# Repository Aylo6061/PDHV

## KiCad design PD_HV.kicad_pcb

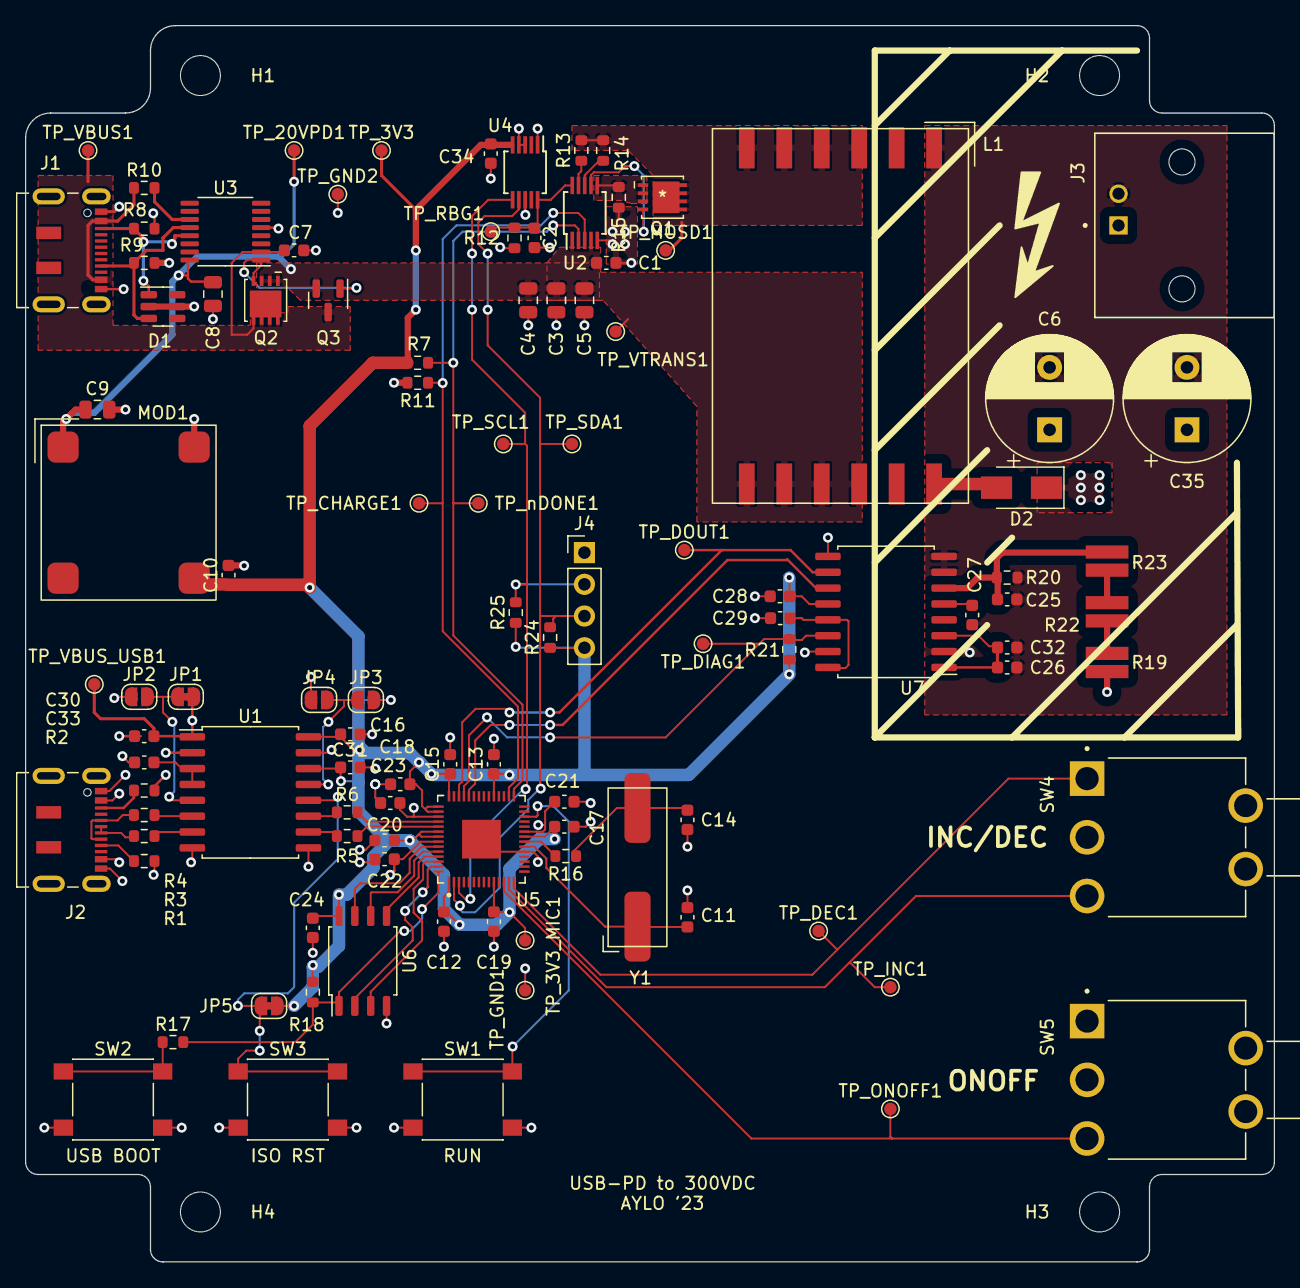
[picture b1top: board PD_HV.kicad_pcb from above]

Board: 4 copper layers, 100.0 x 99.0 mm, 112 parts (0 on the bottom side), 61 nets.

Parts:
C1: 10u; C_0603_1608Metric
C2: 100pF; C_0603_1608Metric
C3, C4, C5: 22uF; C_0805_2012Metric
C6, C35: 3.3u; CP_Radial_D10.0mm_P5.00mm
C7, C12, C21, C26, C28: 1uF; C_0603_1608Metric
C8, C9: 10uF; C_0805_2012Metric
C10: 22uF; C_0603_1608Metric
C11, C14: 27p; C_0603_1608Metric
C13, C15, C16, C17, C18, C19, C20, C22, C23, C24, C27, C29, C30, C31, C32, C33, C34: 100nF; C_0603_1608Metric
C25: 1nF; C_0603_1608Metric
D1: ESDA6V1BC6; SOT-23-6
D2: 600V; D_SMA
H1, H2, H3, H4: MountingHole; MountingHole_3.2mm_M3
J1, J2: USB_C_Receptacle; USB_C_Receptacle_JAE_DX07S016JA1R1500
J3: Conn_Coaxial; TE_5227161-2
J4: Conn_01x04_Male; PinHeader_1x04_P2.54mm_Vertical
JP1, JP5: SolderJumper-2_P1.3mm_Bridged_RoundedPad1.0x1.5mm
JP2, JP3, JP4: SolderJumper-2_P1.3mm_Open_RoundedPad1.0x1.5mm
L1: DA2034-AL
MOD1: K7803JT-500R3-LB; MORNSUN_K7803JT-500R3-LB
Q1: AON7296; DFN3X3A_8L_EPA1_P_AOS
Q2: AON7410; DFN3X3A_8L_EPA1_P_AOS
Q3: AO3400A; SOT-23
R1, R2, R8, R9: 5.1k; R_0603_1608Metric
R3, R4, R5, R6: 24; R_0603_1608Metric
R7, R11, R18: 10k; R_0603_1608Metric
R10: 100k; R_0603_1608Metric
R12: R; R_0603_1608Metric
R13: 12k 1%; R_0603_1608Metric
R14: 43k 1%; R_0603_1608Metric
R15: .024 Ohm 1% 1/3W; R_0603_1608Metric
R16, R17, R20: 1k; R_0603_1608Metric
R19, R22, R23: 100k; RESC1632X60N
R21, R24, R25: 4k7; R_0603_1608Metric
SW1, SW2, SW3: SW_SPST; SW_SPST_PTS645
SW4: MOM-OFF-MOM; SW_100SP1T2B4M6QE
SW5: SW_SPDT; SW_100SP1T2B4M6QE
TP_3V3, TP_3V3_MIC1, TP_20VPD1: TestPoint; TestPoint_Pad_D1.0mm
TP_CHARGE1: TestPoint; TestPoint_Pad_D1.0mm
TP_DEC1: TestPoint; TestPoint_Pad_D1.0mm
TP_DIAG1: TestPoint; TestPoint_Pad_D1.0mm
TP_DOUT1: TestPoint; TestPoint_Pad_D1.0mm
TP_GND1, TP_GND2: TestPoint; TestPoint_Pad_D1.0mm
TP_INC1: TestPoint; TestPoint_Pad_D1.0mm
TP_MOSD1: TestPoint; TestPoint_Pad_D1.0mm
TP_ONOFF1: TestPoint; TestPoint_Pad_D1.0mm
TP_RBG1: TestPoint; TestPoint_Pad_D1.0mm
TP_SCL1: TestPoint; TestPoint_Pad_D1.0mm
TP_SDA1: TestPoint; TestPoint_Pad_D1.0mm
TP_VBUS1: TestPoint; TestPoint_Pad_D1.0mm
TP_VBUS_USB1: TestPoint; TestPoint_Pad_D1.0mm
TP_VTRANS1: TestPoint; TestPoint_Pad_D1.0mm
TP_nDONE1: TestPoint; TestPoint_Pad_D1.0mm
U1: SOIC-16W_7.5x10.3mm_P1.27mm
U2: LT3750A; MSOP-10_3x3mm_P0.5mm
U3: IP2721; TSSOP-16_4.4x5mm_P0.65mm
U4: AD5170BRMZ2.5; MSOP-10_3x3mm_P0.5mm
U5: RP2040; QFN40P700X700X90-57N
U6: W25Q128JVS; SOIC-8_5.23x5.23mm_P1.27mm
U7: AMC3336-Q1; SOIC-16W_7.5x10.3mm_P1.27mm
Y1: Crystal; ABLS-2SMD-XTAL

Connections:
+1V1: C21.1, C22.1, C23.1, U5.23 (DVDD), U5.45 (VREG_VOUT), U5.50 (DVDD)
+3.3V: C10.1, C12.1, C13.1, C15.1, C16.1, C17.1, C18.1, C19.1, C20.1, C24.1, C28.2, C31.1, C34.1, J4.4, JP3.2 (B), JP5.2 (B), MOD1.3 (+Vo_3V3), R7.1, R18.1, R21.1, R24.1, R25.1, TP_3V3.1, TP_3V3_MIC1.1, U1.14 (VDD2), U1.16 (VBUS2), U4.5 (VDD), U5.1 (IOVDD), U5.10 (IOVDD), U5.22 (IOVDD), U5.33 (IOVDD), U5.42 (IOVDD), U5.43 (ADC_AVDD), U5.44 (VREG_VIN), U5.48 (USB_VDD), U5.49 (IOVDD), U6.8 (VCC), U7.12 (VDD)
+20V_USBPD: C1.1, C3.1, C4.1, C5.1, C8.1, C9.1, L1.7, L1.8, L1.9, L1.10, MOD1.1 (+Vin), Q2.1 (S), Q2.2 (S), Q2.3 (S), Q3.2 (S), TP_20VPD1.1, TP_VTRANS1.1, U2.1 (VTRANS), U2.4 (Vcc), U3.16 (VBUS)
+HV: C6.1, C35.1, D2.1 (K), J3.1 (In), R19.1
+VBUS_USB: C30.1, J2.A4 (VBUS), J2.A9 (VBUS), J2.B4 (VBUS), J2.B9 (VBUS), JP1.2 (B), TP_VBUS_USB1.1, U1.1 (VBUS1)
/HVMeasurement/CLKIN: U5.38 (GPIO26/ADC0), U7.11 (CLKIN)
/HVMeasurement/DIAG: R21.2, TP_DIAG1.1, U5.39 (GPIO27/ADC1), U7.14 (DIAG)
/HVMeasurement/DOUT: TP_DOUT1.1, U5.40 (GPIO28/ADC2), U7.10 (DOUT)
/HV_Flyback/CHARGE: R11.1, TP_CHARGE1.1, U2.3 (CHARGE), U5.30 (GPIO19)
/HV_Flyback/RBG: C2.1, R12.1, TP_RBG1.1, U2.10 (RBG), U4.10 (W)
/HV_Flyback/nDone: R7.2, TP_nDONE1.1, U2.2 (nDONE), U5.29 (GPIO18)
/ISO_USB/HOST_DN: J2.A7 (D-), J2.B7 (D-), R4.1
/ISO_USB/HOST_DP: J2.A6 (D+), J2.B6 (D+), R3.1
/ISO_USB/ISO_DN: R6.2, U5.46 (USB_DM)
/ISO_USB/ISO_DP: R5.2, U5.47 (USB_DP)
/ISO_USB/PIN: JP5.1 (A), SW3.1 (A), U1.12 (PIN)
/ISO_USB/VDD1: C33.1, U1.3 (VDD1), U1.4 (PDEN)
/RP2040/DEC: SW4.1, TP_DEC1.1, U5.14 (GPIO11)
/RP2040/INC: SW4.3, TP_INC1.1, U5.13 (GPIO10)
/RP2040/ONOFF: SW5.3, TP_ONOFF1.1, U5.12 (GPIO9)
/RP2040/QSPI_SCLK: U5.52 (QSPI_SCLK), U6.6 (CLK)
/RP2040/QSPI_SD0: U5.53 (QSPI_SD0), U6.5 (DI(IO0))
/RP2040/QSPI_SD1: U5.55 (QSPI_SD1), U6.2 (DO(IO1))
/RP2040/QSPI_SD2: U5.54 (QSPI_SD2), U6.3 (IO2)
/RP2040/QSPI_SD3: U5.51 (QSPI_SD3), U6.7 (IO3)
/RP2040/QSPI_SS: R17.2, R18.2, U5.56 (QSPI_CSN), U6.1 (~CS)
/RP2040/RUN: SW1.1 (A), U5.26 (RUN)
/RP2040/SCL: J4.2, R25.2, TP_SCL1.1, U4.6 (SCL), U5.3 (GPIO1)
/RP2040/SDA: J4.3, R24.2, TP_SDA1.1, U4.7 (SDA), U5.2 (GPIO0)
/RP2040/nUSB_BOOT: R17.1, SW2.1 (A)
/USBPD_IN/CC1: D1.1 (TVS1), J1.A5 (CC1), R8.1, U3.13 (CC1)
/USBPD_IN/CC2: D1.3 (TVS2), J1.B5 (CC2), R9.1, U3.12 (CC2)
/USBPD_IN/VBUSG: Q2.4 (G), Q3.1 (G), U3.1 (VBUSG)
GND: C1.2, C2.2, C3.2, C4.2, C5.2, C7.2, C8.2, C9.2, C10.2, C11.2, C12.2, C13.2, C14.2, C15.2, C16.2, C17.2, C18.2, C19.2, C20.2, C21.2, C22.2, C23.2, C24.2, C28.1, C29.1, C31.2, C34.2, D1.2 (COM), D1.5 (COM), J1.A1 (GND), J1.A12 (GND), J1.B1 (GND), J1.B12 (GND), J4.1, JP4.1 (A), MOD1.4 (GND), R8.2, R9.2, R11.2, R12.2, R15.2, SW1.2 (B), SW2.2 (B), SW3.2 (B), SW4.2, SW5.2, TP_GND1.1, TP_GND2.1, U1.9 (GND2), U1.15 (GND2), U2.5 (GND), U3.5 (GND), U4.1 (B), U4.3 (AD0), U4.4 (GND), U4.8 (AD1), U5.19 (TESTEN), U5.57 (GND), U6.4 (GND), U7.9 (GND), U7.15 (DCDC_GND)
GND1: C30.2, C33.2, J2.A1 (GND), J2.A12 (GND), J2.B1 (GND), J2.B12 (GND), JP2.1 (A), R1.2, R2.2, U1.2 (GND1), U1.8 (GND1)
GND2: C6.2, C25.2, C26.1, C27.1, C32.2, C35.2, J3.2 (Ext), L1.1, R20.2, U7.2 (DCDC_HGND), U7.7 (INN), U7.8 (HGND)
unnamed: C11.1, U5.20 (XIN), Y1.1
unnamed: C14.1, R16.1, Y1.2
unnamed: C25.1, R20.1, R23.2, U7.6 (INP)
unnamed: C26.2, C32.1, U7.1 (DCDC_OUT), U7.3 (HLDO_IN)
unnamed: C27.2, U7.5 (HLDO_OUT)
unnamed: C29.2, U7.13 (LDO_OUT), U7.16 (DCDC_IN)
unnamed: D2.2 (A), L1.12
unnamed: J2.A5 (CC1), R2.1
unnamed: J2.B5 (CC2), R1.1
unnamed: JP1.1 (A), JP2.2 (B), U1.5 (SPU)
unnamed: JP3.1 (A), JP4.2 (B), U1.13 (SPD)
unnamed: L1.3, L1.4, L1.5, L1.6, Q1.5 (D), Q1.6 (D), Q1.7 (D), Q1.8 (D), R13.2, R14.2, TP_MOSD1.1
unnamed: Q1.1 (S), Q1.2 (S), Q1.3 (S), R15.1, U2.6 (SOURCE)
unnamed: Q1.4 (G), U2.7 (GATE)
unnamed: R3.2, U1.7 (UD+)
unnamed: R4.2, U1.6 (UD-)
unnamed: R5.1, U1.10 (DD+)
unnamed: R6.1, U1.11 (DD-)
unnamed: R10.2, U3.11 (SEL)
unnamed: R13.1, U2.9 (RVOUT)
unnamed: R14.1, U2.8 (RDCM)
unnamed: R16.2, U5.21 (XOUT)
unnamed: R19.2, R22.1
unnamed: R22.2, R23.1
VBUS: C7.1, J1.A4 (VBUS), J1.A9 (VBUS), J1.B4 (VBUS), J1.B9 (VBUS), Q2.5 (D), Q2.6 (D), Q2.7 (D), Q2.8 (D), Q3.3 (D), R10.1, TP_VBUS1.1, U3.2 (VIN)

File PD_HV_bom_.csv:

Component,Description,Part,References,Value,Footprint,Quantity Per PCB,Datasheet,MPN,Voltage,Digikey PN,Tol,MANUFACTURER,MAXIMUM_PACKAGE_HEIGHT,PARTREV,STANDARD
1,Unpolarized capacitor,C,C11 C14,27p,C_0603_1608Metric,2,~,CC0603JRNPO9BN270,,,,,,,
2,Unpolarized capacitor,C,C2,100pF,C_0603_1608Metric,1,~,CL10C101JB8NNNC,50V,,,,,,
3,Unpolarized capacitor,C,C25,1nF,,1,~,CL10B102KB8NNWC,,,,,,,
4,Unpolarized capacitor,C,C13 C15 C17 C18 C19 C20 C22 C23 C24 C34,100nF,C_0603_1608Metric,10,~,CC0603KRX7R6BB104,10V,,,,,,
5,Unpolarized capacitor,C,C16 C30 C31 C33,100nF,,4,~,CC0603KRX7R6BB104,10V,,,,,,
6,Unpolarized capacitor,C,C27 C29 C32,100nF,,3,~,CL10B104KB8NNWC,50V,,,,,,
7,Unpolarized capacitor,C,C12 C21,1uF,C_0603_1608Metric,2,~,CL10B105KP8NNNC,10V,,,,,,
8,Unpolarized capacitor,C,C26 C28,1uF,,2,~,CL10A105KB8NNNC,50V,,,,,,
9,Unpolarized capacitor,C,C7,1uF,C_0603_1608Metric,1,~,UMK107BJ105KA-T,25V,,,,,,
10,"Polarized capacitor, US symbol",C_Polarized_US,C6 C35,3.3u,CP_Radial_D10.0mm_P5.00mm,2,~,860021375011,400V,,,,,,
11,Unpolarized capacitor,C,C1,10u,C_0603_1608Metric,1,~,CL21A106KAYNNNG,25V,,,,,,
12,Unpolarized capacitor,C,C8 C9,10uF,C_0805_2012Metric,2,~,GRM21BR61H106KE43L,50V,,,,,,
13,Unpolarized capacitor,C,C10,22uF,C_0603_1608Metric,1,~,CL10A226MP8NUNE,10V,,,,,,
14,Unpolarized capacitor,C,C3 C4 C5,22uF,C_0805_2012Metric,3,~,CL21A226MAYNNNE,25V,,,,,,
15,Diode,D,D2,600V,D_SMA,1,~,ES1J,600V,1655-ES1JCT-ND,,,,,
16,"Quad bidirectional transil, Suppressor for ESD protection, 5V Standoff, 4 Channels, SOT-23-6",ESDA6V1BC6,D1,ESDA6V1BC6,SOT-23-6,1,http://www.st.com/content/ccc/resource/technical/document/da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,ESDA6V1BC6,,,,,,,
17,"Generic connector, single row, 01x04, script generated (kicad-library-utils/schlib/autogen/connector/)",Conn_01x04_Male,J4,Conn_01x04_Male,PinHeader_1x04_P2.54mm_Vertical,1,~,,,,,,,,
18,"coaxial connector (BNC, SMA, SMB, SMC, Cinch/RCA, LEMO, ...)",Conn_Coaxial,J3,Conn_Coaxial,TE_5227161-2,1, ~,5227161-2,,,,,,,
19,USB Full-Featured Type-C Receptacle connector,USB_C_Receptacle,J1,USB_C_Receptacle,USB_C_Receptacle_JAE_DX07S016JA1R1500,1,https://www.usb.org/sites/default/files/documents/usb_type-c.zip,DX07S016JA1R1500,,,,,,,
20,USB Full-Featured Type-C Receptacle connector,USB_C_Receptacle,J2,USB_C_Receptacle,,1,https://www.usb.org/sites/default/files/documents/usb_type-c.zip,DX07S016JA1R1500,,,,,,,
21,"Solder Jumper, 2-pole, open",SolderJumper_2_Open,JP2 JP4,~,,2,~,DNP,,,,,,,
22,Flyback transformer 10:1 5A max,DA2034-AL,L1,DA2034-AL,DA2034-AL,1,,DA2034-AL,,,,,,,
23,,K7803JT-500R3-LB,MOD1,K7803JT-500R3-LB,MORNSUN_K7803JT-500R3-LB,1,,K7803JT-500R3-LB,,,,,,,
24,"30V Vds, 5.7A Id, N-Channel MOSFET, SOT-23",AO3400A,Q3,AO3400A,SOT-23,1,http://www.aosmd.com/pdfs/datasheet/AO3400A.pdf,AO3400A,,,,,,,
25,,AON7296,Q1,AON7296,DFN3X3A_8L_EPA1_P_AOS,1,,AON7296,,,,,,,
26,,AON7410,Q2,AON7410,DFN3X3A_8L_EPA1_P_AOS,1,,AON7410,,,,,,,
27,Resistor,R,R3 R4 R5 R6,24,,4,~,RMCF0603FT24R0,,RMCF0603FT24R0CT-ND,1%,,,,
28,Resistor,R,R16 R17,1k,R_0603_1608Metric,2,~,RMCF0603FT1K00,,RMCF0603FT1K00CT-ND,,,,,
29,Resistor,R,R20,1k,,1,~,RMCF0603FT1K00,,RMCF0603FT1K00CT-ND,,,,,
30,Resistor,R,R21 R24 R25,4k7,R_0603_1608Metric,3,~,RC0603FR-074K7L,,311-4.70KHRCT-ND,,,,,
31,Resistor,R,R1 R2,5.1k,,2,~,RMCF0603FT5K10,,RMCF0603FT5K10CT-ND,1%,,,,
32,Resistor,R,R8 R9,5.1k,R_0603_1608Metric,2,~,RMCF0603FT5K10,,RMCF0603FT5K10CT-ND,1%,,,,
33,Resistor,R,R7 R11 R18,10k,R_0603_1608Metric,3,~,RMCF0603JT10K0,,,,,,,
34,Resistor,R,R10,100k,R_0603_1608Metric,1,~,RMCF0603JG100K,,RMCF0603JG100KCT-ND,,,,,
35,Resistor,R,R19 R22 R23,100k,,3,~,RMCF0603FT300K,,PRG3216P-1003-D-T5,,,,,
36,Resistor,R,R15,.024 Ohm 1% 1/3W,R_0603_1608Metric,1,~,WFCP0603R0240FE66,,541-WFCP0603R0240FE66CT-ND,,,,,
37,Resistor,R,R13,12k 1%,R_0603_1608Metric,1,~,RMCF0603FT12K0,,RMCF0603FT12K0CT-ND,,,,,
38,Resistor,R,R14,43k 1%,R_0603_1608Metric,1,~,RC0603FR-0743KL,,311-43.0KHRCT-ND,,,,,
39,Resistor,R,R12,R,R_0603_1608Metric,1,~,DNP,,,,,,,
40,"Switch, three position, single pole triple throw, 3 position switch, SP3T, MOM-OFF-MOM",MOM-OFF-MOM,SW4,MOM-OFF-MOM,SW_100SP1T2B4M6QE,1,~,100SP4T2B4M6RE,,,,,,,
41,"Switch, two position, single pole dual throw, 2 position switch, SP2T",SW_SPDT,SW5,SW_SPDT,SW_100SP1T2B4M6QE,1,~,100SP1T2B4M6QE,,,,,,,
42,Single Pole Single Throw (SPST) switch,SW_SPST,SW1 SW2,SW_SPST,SW_SPST_PTS645,2,~,PTS645SL43SMTR92 LFS,,,,,,,
43,Single Pole Single Throw (SPST) switch,SW_SPST,SW3,SW_SPST,,1,~,PTS645SL43SMTR92 LFS,,,,,,,
44,,AD5170BRMZ2.5,U4,AD5170BRMZ2.5,MSOP-10_3x3mm_P0.5mm,1,,AD5170BRMZ2.5,,,,,,,
45,,AMC3336-Q1,U7,AMC3336-Q1,,1,,AMC3336-Q1,,,,,,,
46,,IP2721,U3,IP2721,TSSOP-16_4.4x5mm_P0.65mm,1,,IP2721,,,,,,,
47,,LT3750A,U2,LT3750A,MSOP-10_3x3mm_P0.5mm,1,,LT3750A,,,,,,,
48,,RP2040,U5,RP2040,QFN40P700X700X90-57N,1,,RP2040,,,,Raspberry Pi,0.9 mm,1.6.1,IPC 7351B
49,"128Mb Serial Flash Memory, Standard/Dual/Quad SPI, SOIC-8",W25Q128JVS,U6,W25Q128JVS,SOIC-8_5.23x5.23mm_P1.27mm,1,http://www.winbond.com/resource-files/w25q128jv_dtr%20revc%2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,W25Q128JVS,,,,,,,
50,"Full/Low Speed, iCoupler USB Digital Isolator, 2.5kV protection",ADUM3160,U1,~,SOIC-16W_7.5x10.3mm_P1.27mm,1,https://www.analog.com/media/en/technical-documentation/data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,ADUM3160,,,,,,,
51,Two pin crystal,Crystal,Y1,Crystal,ABLS-2SMD-XTAL,1,~,ABLS-12.000MHZ-B4-T,,535-10218-1-ND,,,,,





Component Groups:,51
Component Count:,86
Fitted Components:,86
Number of PCBs:,1
Total components:,86
Schematic Version:,
Schematic Date:,
PCB Variant:,default
BoM Date:,3/28/2023 9:39:27 PM
Schematic Source:,PD_HV.kicad_sch
KiCad Version:,Eeschema (6.0.4)

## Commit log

2023-03-27 setting up repo.
2023-03-27 inial commit of mostly done project
2023-03-29 finished routing, sending to fab

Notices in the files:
parts and their libraries:
Copyright 2021 Accelerated Designs. All rights reserved.
